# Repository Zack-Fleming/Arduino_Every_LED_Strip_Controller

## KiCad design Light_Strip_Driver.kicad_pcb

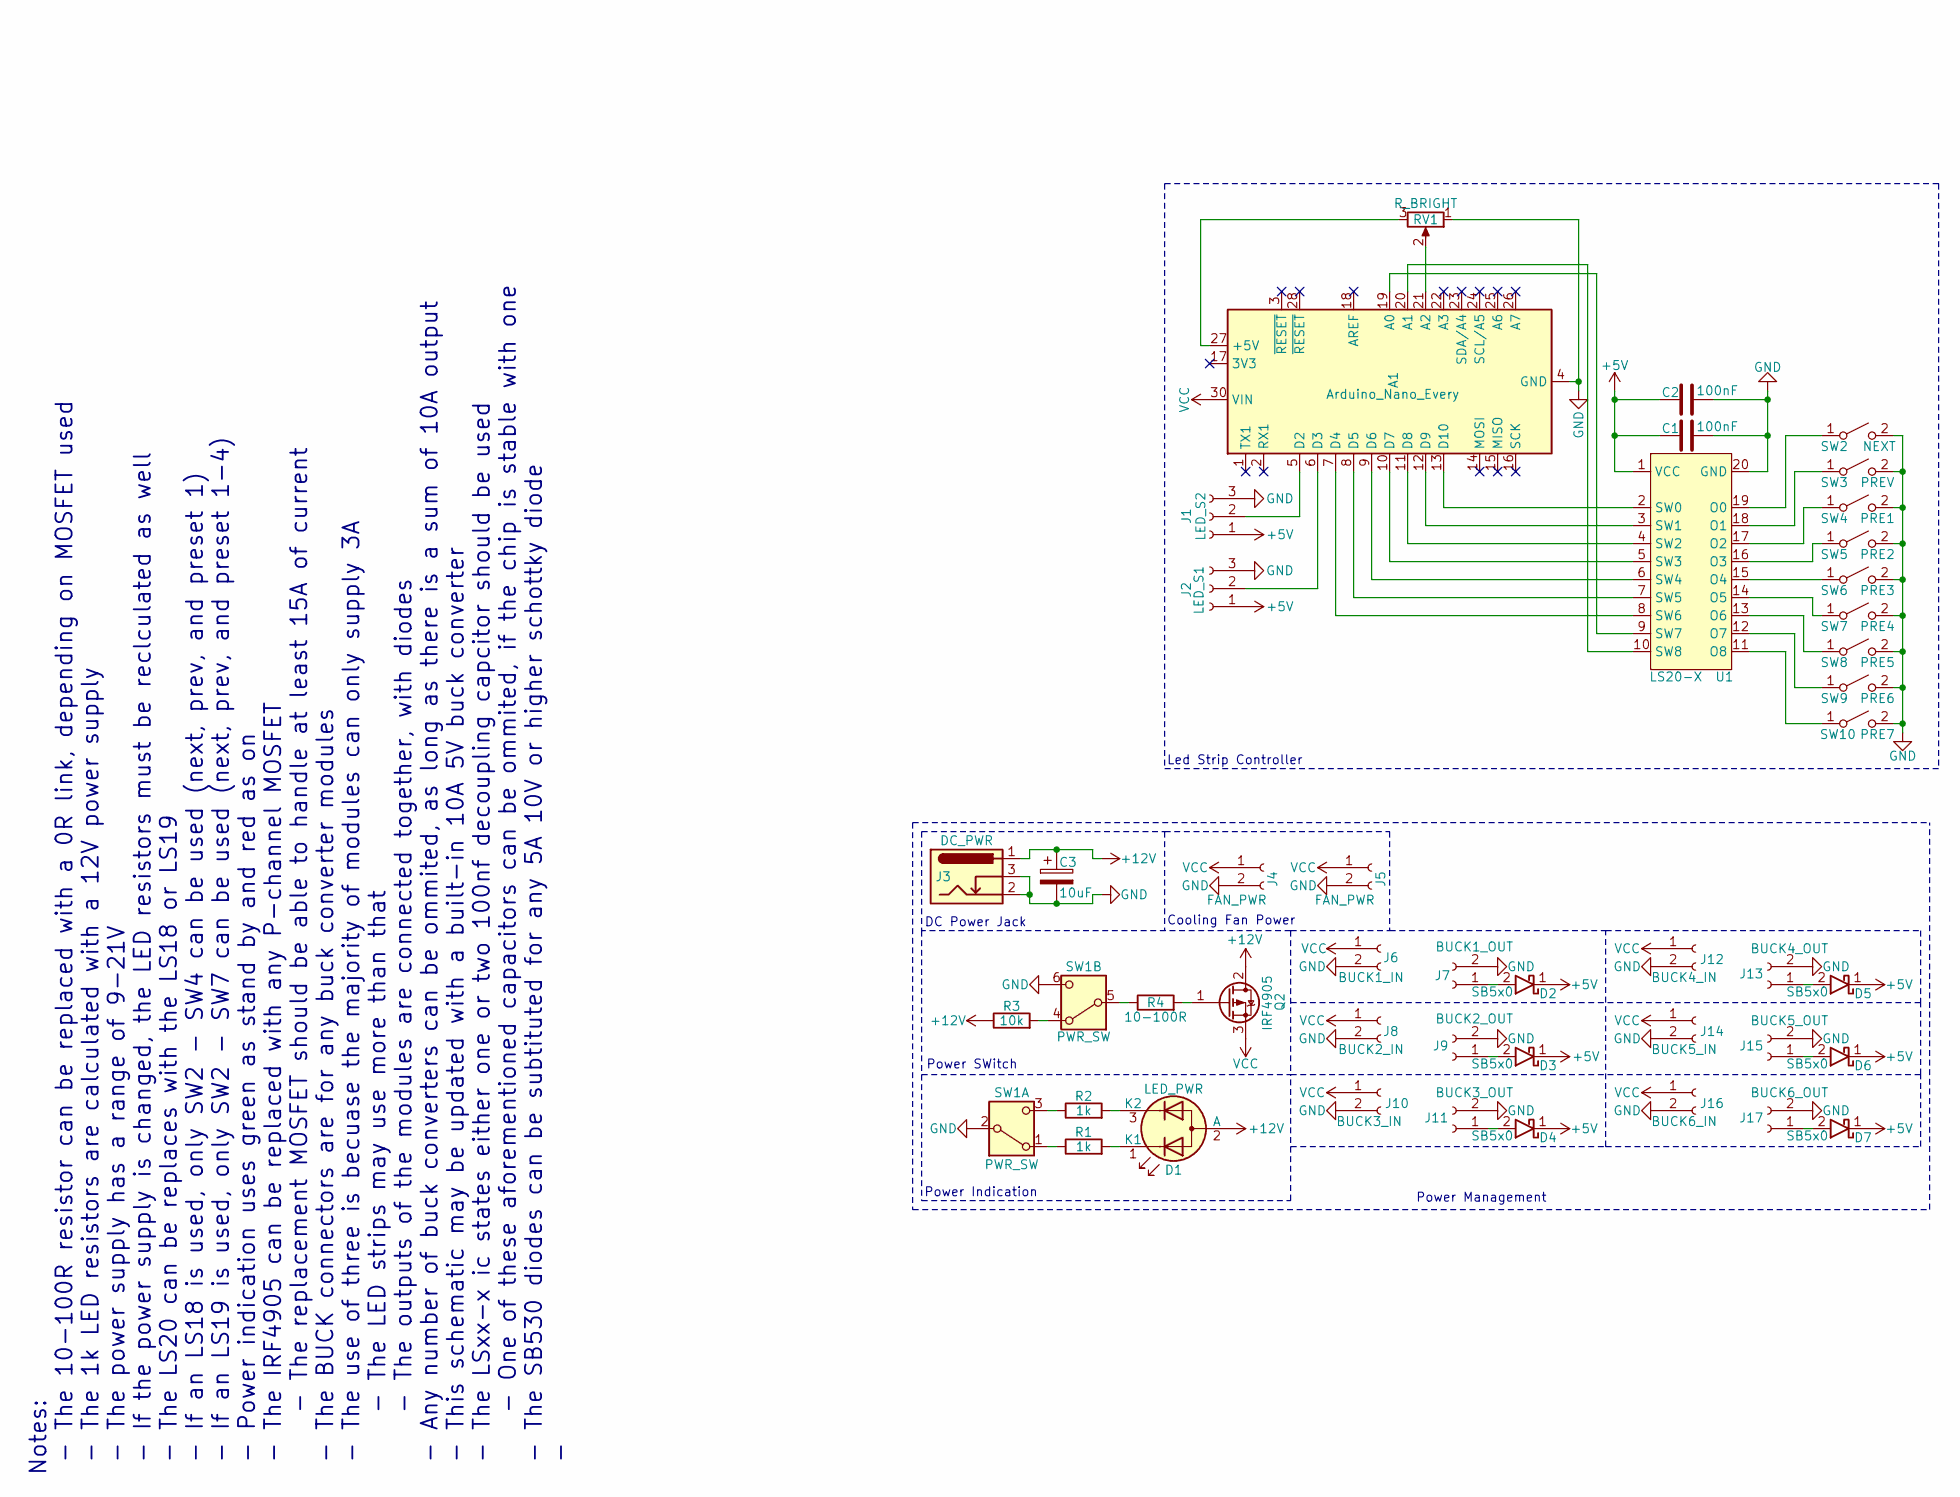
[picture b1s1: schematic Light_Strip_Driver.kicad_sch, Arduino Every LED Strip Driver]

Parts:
A1: Arduino_Nano_Every; Arduino_Nano
C1, C2: 100nF; C_1206_3216Metric_Pad1.33x1.80mm_HandSolder
C3: 10uF; CP_Radial_D5.0mm_P2.00mm
D1: LED_PWR; LED_D5.0mm-3
D2, D3, D4, D5, D6, D7: SB5x0; D_DO-201AD_P12.70mm_Horizontal
J1: LED_S2; PinSocket_1x03_P2.54mm_Vertical
J2: LED_S1; PinSocket_1x03_P2.54mm_Vertical
J3: DC_PWR; BarrelJack_Horizontal
J4, J5: FAN_PWR; PinSocket_1x02_P2.54mm_Vertical
J6: BUCK1_IN; PinSocket_1x02_P2.54mm_Vertical
J7: BUCK1_OUT; PinSocket_1x02_P2.54mm_Vertical
J8: BUCK2_IN; PinSocket_1x02_P2.54mm_Vertical
J9: BUCK2_OUT; PinSocket_1x02_P2.54mm_Vertical
J10: BUCK3_IN; PinSocket_1x02_P2.54mm_Vertical
J11: BUCK3_OUT; PinSocket_1x02_P2.54mm_Vertical
J12: BUCK4_IN; PinSocket_1x02_P2.54mm_Vertical
J13: BUCK4_OUT; PinSocket_1x02_P2.54mm_Vertical
J14: BUCK5_IN; PinSocket_1x02_P2.54mm_Vertical
J15: BUCK5_OUT; PinSocket_1x02_P2.54mm_Vertical
J16: BUCK6_IN; PinSocket_1x02_P2.54mm_Vertical
J17: BUCK6_OUT; PinSocket_1x02_P2.54mm_Vertical
Q2: IRF4905; TO-220-3_Vertical
R1, R2: 1k; R_Axial_DIN0207_L6.3mm_D2.5mm_P2.54mm_Vertical
R3: 10k; R_Axial_DIN0207_L6.3mm_D2.5mm_P2.54mm_Vertical
R4: 10-100R; R_Axial_DIN0207_L6.3mm_D2.5mm_P2.54mm_Vertical
RV1: R_BRIGHT; P120_pot_Vertical
SW1: PWR_SW; DPDT_E_Switch_400U_Horizontal
SW2: NEXT; SW_PUSH_6mm
SW3: PREV; SW_PUSH_6mm
SW4: PRE1; SW_PUSH_6mm
SW5: PRE2; SW_PUSH_6mm
SW6: PRE3; SW_PUSH_6mm
SW7: PRE4; SW_PUSH_6mm
SW8: PRE5; SW_PUSH_6mm
SW9: PRE6; SW_PUSH_6mm
SW10: PRE7; SW_PUSH_6mm
U1: LS20-X; DIP-20_W7.62mm_LongPads

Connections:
+5V: C1.1, C2.1, D2.1, D3.1, D4.1, D5.1, D6.1, D7.1, J1.1, J2.1, U1.1 (VCC)
+12V: C3.1, D1.2 (A), J3.1, Q2.2 (D), R3.1
GND: A1.4 (GND), A1.29 (GND), C1.2, C2.2, C3.2, J1.3, J2.3, J3.2, J3.3, J4.2, J5.2, J6.2, J7.2, J8.2, J9.2, J10.2, J11.2, J12.2, J13.2, J14.2, J15.2, J16.2, J17.2, RV1.1, SW1.2 (B), SW1.6 (C), SW2.2 (B), SW3.2 (B), SW4.2 (B), SW5.2 (B), SW6.2 (B), SW7.2 (B), SW8.2 (B), SW9.2 (B), SW10.2 (B), U1.20 (GND)
unnamed: A1.27 (+5V), RV1.3
unnamed: A1.19 (A0), U1.9 (SW7)
unnamed: A1.20 (A1), U1.10 (SW8)
unnamed: A1.21 (A2), RV1.2
unnamed: A1.5 (D2), J1.2
unnamed: A1.6 (D3), J2.2
unnamed: A1.7 (D4), U1.8 (SW6)
unnamed: A1.8 (D5), U1.7 (SW5)
unnamed: A1.9 (D6), U1.6 (SW4)
unnamed: A1.10 (D7), U1.5 (SW3)
unnamed: A1.11 (D8), U1.4 (SW2)
unnamed: A1.12 (D9), U1.3 (SW1)
unnamed: A1.13 (D10), U1.2 (SW0)
unnamed: D1.1 (K1), R1.2
unnamed: D1.3 (K2), R2.2
unnamed: D2.2, J7.1
unnamed: D3.2, J9.1
unnamed: D4.2, J11.1
unnamed: D5.2, J13.1
unnamed: D6.2, J15.1
unnamed: D7.2, J17.1
unnamed: Q2.1 (G), R4.2
unnamed: R1.1, SW1.1 (A)
unnamed: R2.1, SW1.3 (C)
unnamed: R3.2, SW1.4 (A)
unnamed: R4.1, SW1.5 (B)
unnamed: SW2.1 (A), U1.19 (O0)
unnamed: SW3.1 (A), U1.18 (O1)
unnamed: SW4.1 (A), U1.17 (O2)
unnamed: SW5.1 (A), U1.16 (O3)
unnamed: SW6.1 (A), U1.15 (O4)
unnamed: SW7.1 (A), U1.14 (O5)
unnamed: SW8.1 (A), U1.13 (O6)
unnamed: SW9.1 (A), U1.12 (O7)
unnamed: SW10.1 (A), U1.11 (O8)
VCC: A1.30 (VIN), J4.1, J5.1, J6.1, J8.1, J10.1, J12.1, J14.1, J16.1, Q2.3 (S)

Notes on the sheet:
Led Strip Controller
Power Indication
DC Power Jack
Notes: - The 10-100R resistor can be replaced with a 0R link, depending on MOSFET used - The 1k LED resistors are calculated with a 12V power supply - The power supply has a range of 9-21V - If the power supply is changed, the LED resistors must be reclculated as well - The LS20 can be replaces wit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
Cooling Fan Power
Power SWitch
Power Management

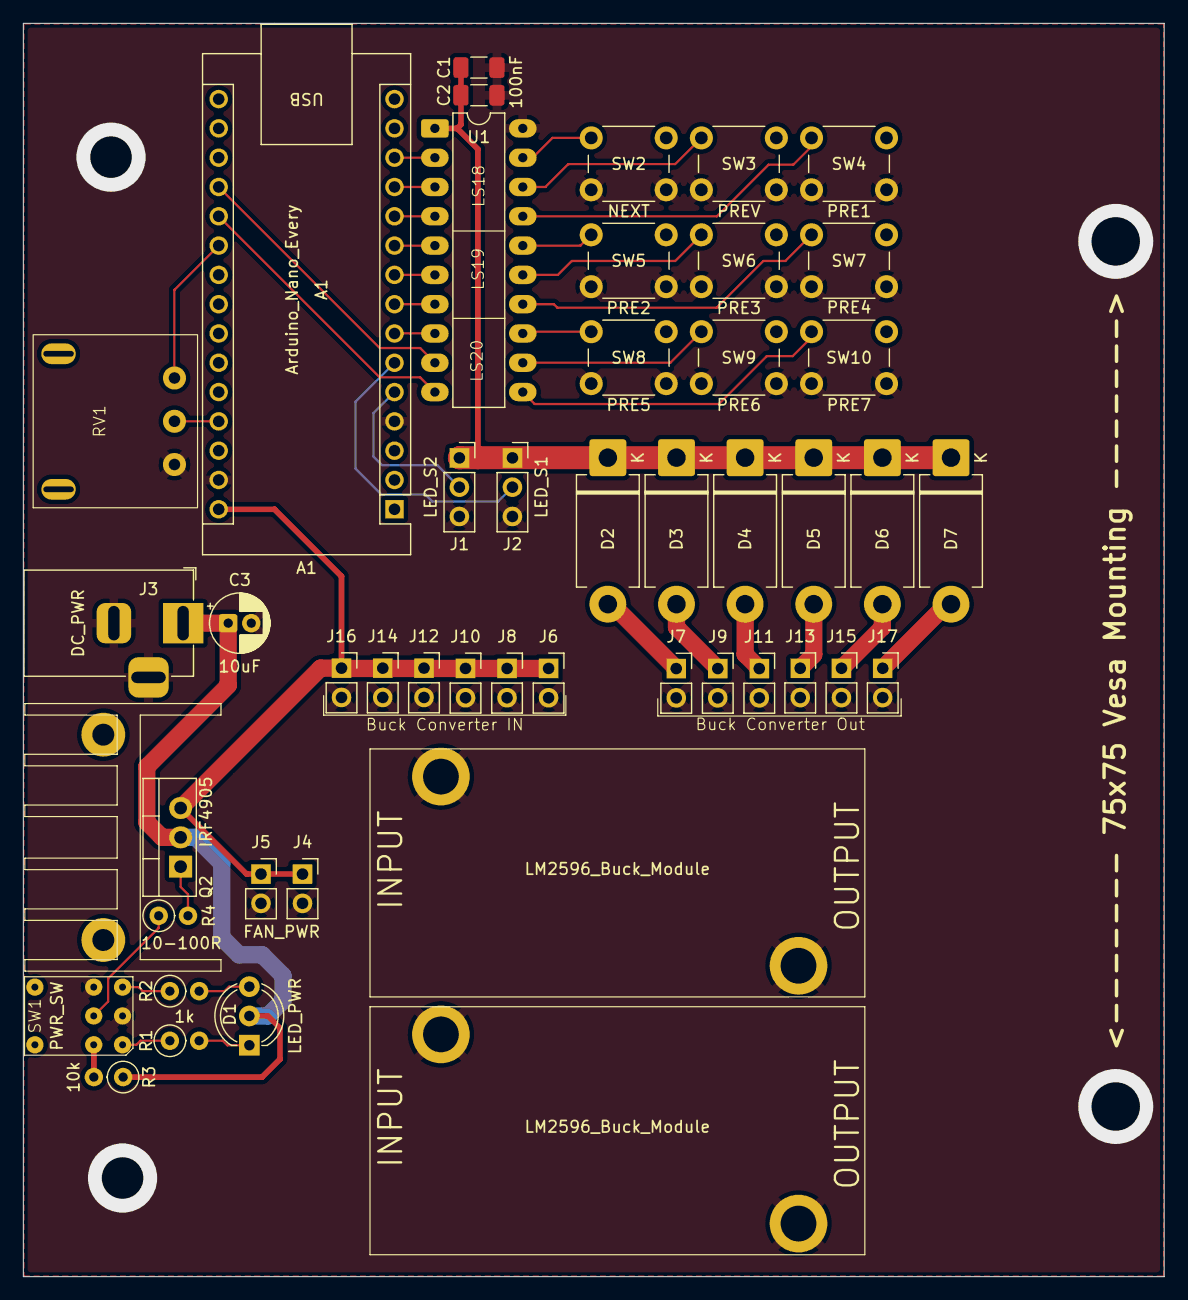
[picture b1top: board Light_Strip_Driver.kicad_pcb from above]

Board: 2 copper layers, 98.9 x 108.6 mm, 45 parts (0 on the bottom side), 39 nets.

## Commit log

2026-05-07 inital commit
2026-05-09 worked on pcb layout
2026-05-09 added relavent library files
2026-05-11 finished pcb design
